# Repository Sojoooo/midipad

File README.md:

<h1>
  <br>
  MIDIPad
  <br>
</h1>

This little midipad will help me access easily some of my music production software's functionalities.

## Schematic and PCB

I designed it with Kicad:

Schematic:

<br>

PCB:

## Case

The case includes:

- 3D printed parts: a base and a top cover
- Assembled with 4x M3 bolts and 4x M3 heatset inserts

Designed in Fusion 360:

## BOM

- 6x Cherry MX Switches
- 6x Keycaps
- 4x M3x5x4 Heatset Inserts
- 4x M3 Bolts
- 1x 128x32 0.91" OLED Display
- 2x EC11 Rotary Encoders
- 1x XIAO RP2040
- 1x Case (2 printed parts)

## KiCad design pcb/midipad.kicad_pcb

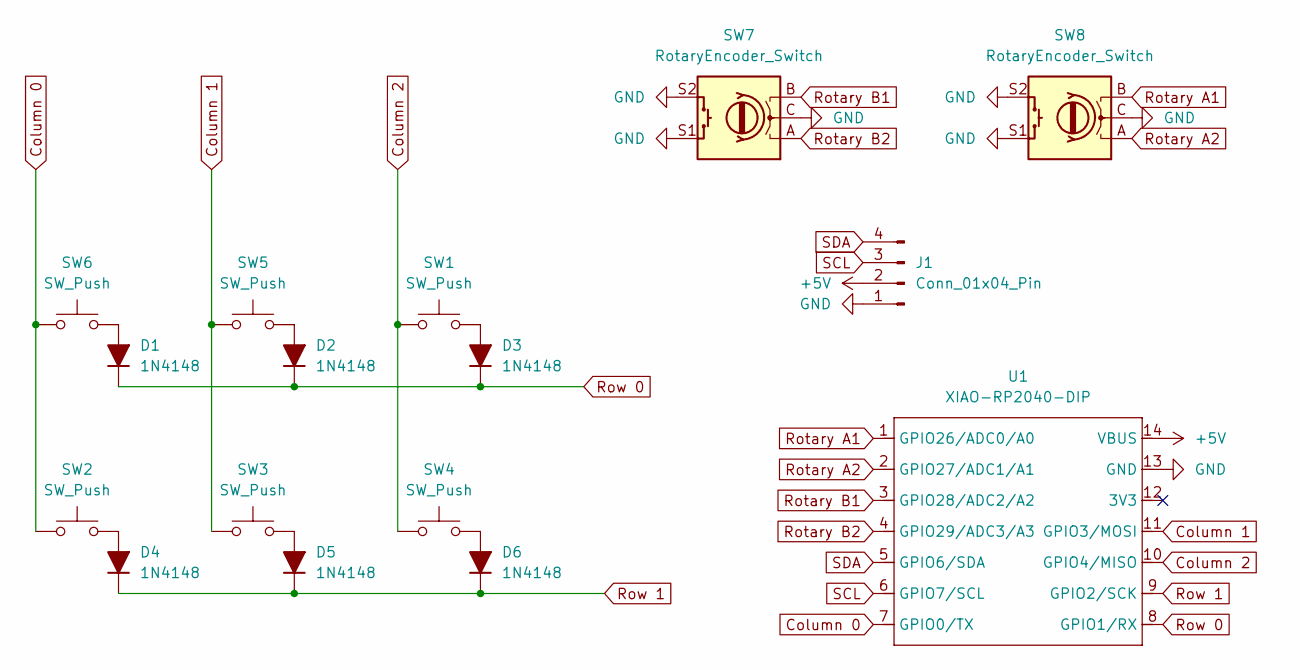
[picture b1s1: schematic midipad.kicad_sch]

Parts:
D1, D2, D3, D4, D5, D6: 1N4148; D_DO-35_SOD27_P7.62mm_Horizontal
J1: Conn_01x04_Pin; SSD1306-0.91-OLED-4pin-128x32
SW1, SW2, SW3, SW4, SW5, SW6: SW_Push; SW_Cherry_MX_1.00u_PCB
SW7, SW8: RotaryEncoder_Switch; RotaryEncoder_Alps_EC11E-Switch_Vertical_H20mm
U1: XIAO-RP2040-DIP

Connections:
+5V: J1.2, U1.14 (VBUS)
Column 0: SW2.1, SW6.1, U1.7 (GPIO0/TX)
Column 1: SW3.1, SW5.1, U1.11 (GPIO3/MOSI)
Column 2: SW1.1, SW4.1, U1.10 (GPIO4/MISO)
GND: J1.1, SW7.C, SW7.S1, SW7.S2, SW8.C, SW8.S1, SW8.S2, U1.13 (GND)
unnamed: D1.2 (A), SW6.2
unnamed: D2.2 (A), SW5.2
unnamed: D3.2 (A), SW1.2
unnamed: D4.2 (A), SW2.2
unnamed: D5.2 (A), SW3.2
unnamed: D6.2 (A), SW4.2
Rotary A1: SW8.B, U1.1 (GPIO26/ADC0/A0)
Rotary A2: SW8.A, U1.2 (GPIO27/ADC1/A1)
Rotary B1: SW7.B, U1.3 (GPIO28/ADC2/A2)
Rotary B2: SW7.A, U1.4 (GPIO29/ADC3/A3)
Row 0: D1.1 (K), D2.1 (K), D3.1 (K), U1.8 (GPIO1/RX)
Row 1: D4.1 (K), D5.1 (K), D6.1 (K), U1.9 (GPIO2/SCK)
SCL: J1.3, U1.6 (GPIO7/SCL)
SDA: J1.4, U1.5 (GPIO6/SDA)

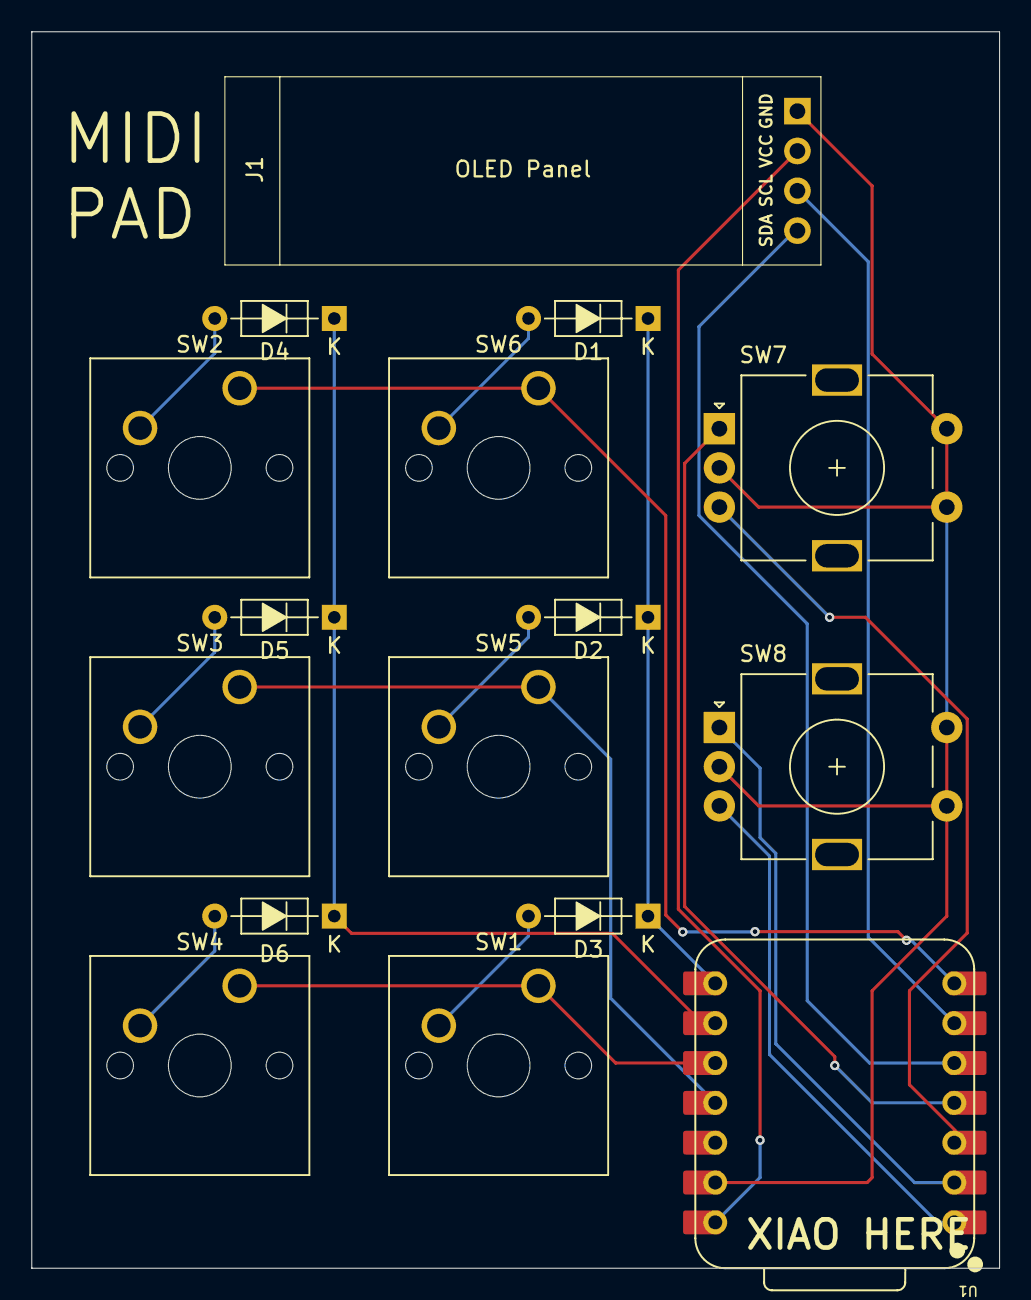
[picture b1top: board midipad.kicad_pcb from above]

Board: 2 copper layers, 61.7 x 78.8 mm, 16 parts (0 on the bottom side), 19 nets.

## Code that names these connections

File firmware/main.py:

# You import all the IOs of your board
import board

# These are imports from the kmk library
from kmk.kmk_keyboard import KMKKeyboard
from kmk.scanners.keypad import KeysScanner
from kmk.keys import KC
from kmk.modules.macros import Press, Release, Tap, Macros

from kmk.scanners import DiodeOrientation

COL_PINS = (board.GPIO0, board.GPIO3, board.GPIO4)
ROW_PINS = (board.GPIO1, board.GPIO2)

# This is the main instance of your keyboard
keyboard = KMKKeyboard()

# Add the macro extension
macros = Macros()
keyboard.modules.append(macros)

keyboard.matrix = MatrixScanner(
    row_pins=ROW_PINS,
    col_pins=COL_PINS,
    diode_orientation=MatrixScanner.DIODE_COL2ROW,
)

# Here you define the buttons corresponding to the pins
# Look here for keycodes: https://github.com/KMKfw/kmk_firmware/blob/main/docs/en/keycodes.md
# And here for macros: https://github.com/KMKfw/kmk_firmware/blob/main/docs/en/macros.md
keyboard.keymap = [
    [KC.1, KC.2, KC.3, KC.4, KC.5, KC.6]
]

# Start kmk!
if __name__ == '__main__':
    keyboard.go()

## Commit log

2025-07-10 OH YEAH
2025-07-11 firmware
2025-07-11 READme
2025-07-11 READMe2
